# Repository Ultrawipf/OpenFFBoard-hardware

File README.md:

# OpenFFBoard-hardware
This contains the hardware designs of the OpenFFBoard

These are work in progress.
No guarantee for functionality or safety! The designs are experimental and may change at any time.
The firmware is available in the main [OpenFFBoard](https://github.com/Ultrawipf/OpenFFBoard) git.

This project requires soldering of many fine pitched parts including QFN. Availability of components may change over time so check for alternatives if something is not available.
The motor driver should be made with 2oz copper layers for best thermal performance!

The firmware may run on some third party development kits but as they have different pinouts and missing peripherals this is not recommended.

## Buy official kits
* [Elecrow](https://www.elecrow.com/open-ffboard-stm32f407-usb-interface-only.html)
* [Lectronz](https://www.lectronz.com/stores/gigawipf)
* [Tindie](https://www.tindie.com/stores/gigawipf/) or Discord.

Check the [Discord](https://discord.com/invite/gHtnEcP) and [project page](https://hackaday.io/project/163904-open-ffboard) for updates.

---

### LICENSE NOTE: The root license applies to all subfolders NOT containing their own LICENSE file. If a subfolder contains a different LICENSE file this different license applies to all subfolders below this LICENSE file.

**If you want to sell any hardware of this project yourself i would kindly ask you to get in contact with me ([mail](mailto:ffboard@y-richter.de) or Discord)**

## Changelog
### TMC Driver:

#### 1.1: (Prerelease prototype)
- Added filtering for Hall and Encoder inputs.
- Separated TMC and STM VM sense dividers

#### 1.2: (Major redesign)
- Using TMC4671-LA production version
- Added 5V buck converter
- Added emergency shutdown method by pulling enable low
- Rotated power stage. Moved all motor connectors to one side
- Moved analog encoder pins and routed differential inputs out
- Improved vcore impedance
- Increased encoder filter frequencies
- Reduced resistance of sense dividers
- Switched LM5050 to LM74700
- Space for 2 VM capacitors
- Improved mosfet protection
- Added temperature sensor pads on AGPI-B
- 50x50+100mm screw holes

#### 1.2 fix:
- Fixed silkscreen (R18 and R19 swapped)
- Modified some labels
- Added 33k gate pulldown for brake resistor
- Moved and resized vias in motor driver part (Manufacturing reliability)
- Tented vias

#### 1.2.2 (HALL):
- Redesigned power stage to use hall sensors (LEM GO SME and TMCS1100)
- Changed buffers to 74LV17APWJ
- Added opamp for TMC inputs (temperature and voltage sensing)
- Used opamp as comparator for hardware brake resistor activation point (~65V)
  
### 1.3.3:
- Analog section with separate LDO
- Support for more current sensors (ACS724)
- Optimized gate driver circuit w. resistors and diodes
- More separation between analog and power sections

### STM USB Interface:
#### 1.1:
- Initial prototype
- STM32F411RE based
- Only supports TMC4671 driver
- Only one SPI2 CS

#### 1.2:
- STM32F407VG
- Reserved PWM pins
- 3 CS pins per SPI
- CAN bus
- Reserved E-Stop
- USB Vbus sense
- separated ADCs for vsense and analog in
- LEDs moved
- Added FFBoard logo
- Changed USB diode to SMC
- Added zener pad on 5V
- Removed encoder buffer
- Higher value pwr led resistor

#### 1.2.1:
- Fixed some labels
- Moved USB socket and terminals slightly to the corners (Big usb plugs might interfere with the pins)
- Changed crystal load capacitors to lower values. (F407 DFU is very sensitive and does not work reliably with too high value caps)
- Added E-Stop capacitor against noise triggering it
- Tented vias

#### 1.2.2
- Swapped (Previously unused) Encoder Z pin from pin 65 to pin 62 because of interrupt conflicts with the DRV flag pin

#### 1.2.3
- USB-C instead of micro USB
- SPI1 uses a 2 row header
- Additional USB protections

#### 1.2.4
- Moved EXT header slightly
- Used 2 extra jumper pins for CAN termination instead of solderjumper

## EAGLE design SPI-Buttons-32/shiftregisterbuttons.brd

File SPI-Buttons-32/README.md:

# Shift register button module

This module allows the connection of up to 32 (or more if chained) buttons to any spi capable microcontroller or as a button source in the OpenFFBoard firmware.

### Connections
* V+ - 3,3V (or 5V)
* OUT - MISO of controller
* CS (Latch) - CS pin of controller
* CLK - SCK
* GND - GND

* IN - OUT of previous module
* Buttons between GND and any input pin

### Configuration in OpenFFBoard

Select SPI button source, select 74HC165 mode and invert buttons and the amount of used buttons (up to 32 for 1, up to 64 for 2 modules)

### CS options

In the default configuration MISO is active with CS HIGH (Bare 74HC165 compatible mode).
Connecting R34 instead of R33 changes this to CS LOW active (SPI compatible mode).
The tristate output mode can be disabled by removing R35.

Mode | R33 | R34 | R35
-|-|-|-
CS HIGH w. tristate | ✅ | ❌ | ✅
CS LOW w. tristate | ❌ | ✅ | ✅
CS HIGH wo. tristate | ✅ | ❌ | ❌
CS HIGH wo. tristate | ❌ | ✅ | ❌

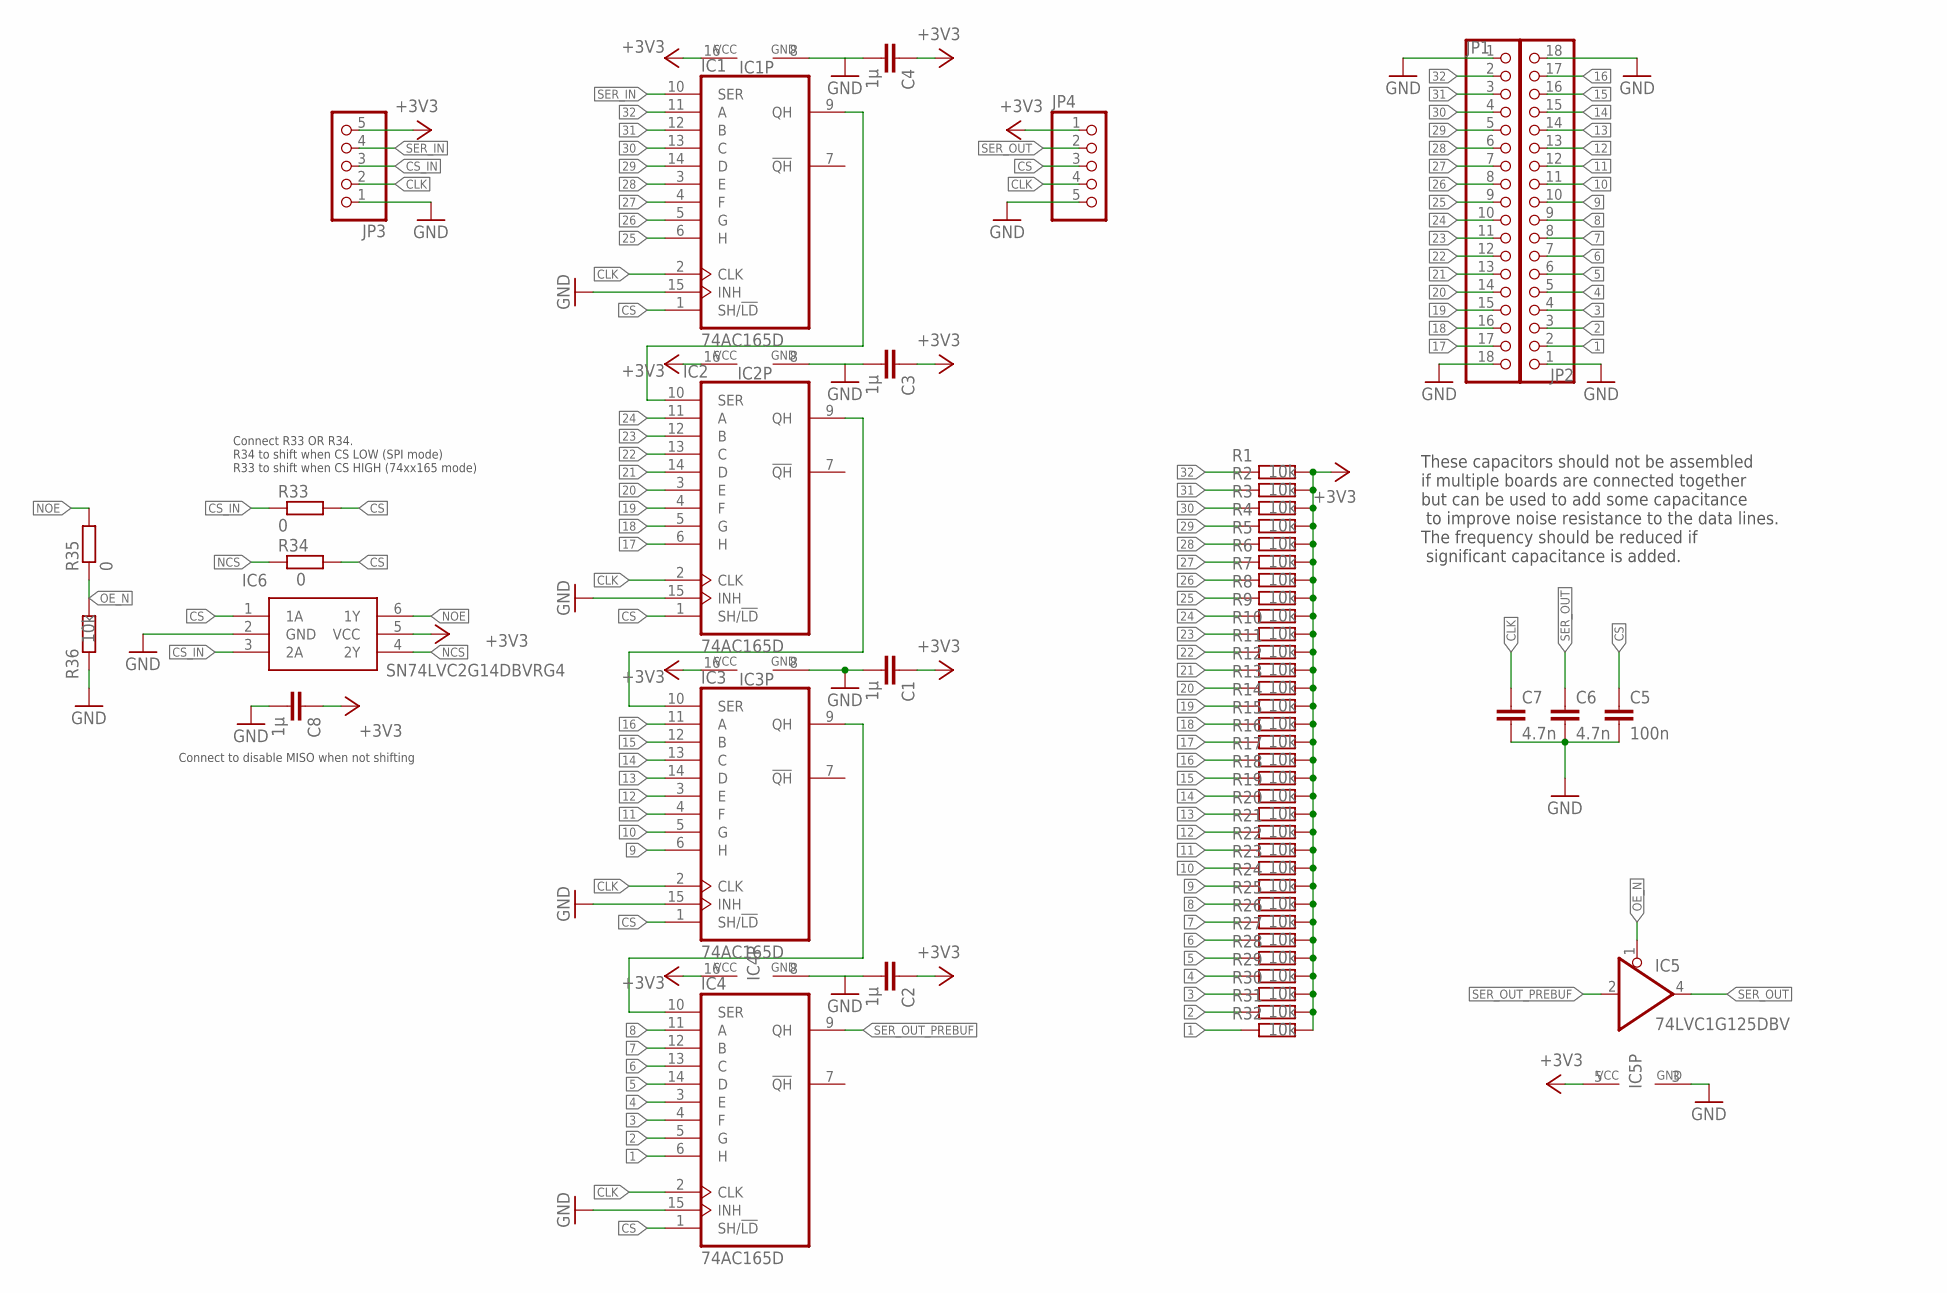
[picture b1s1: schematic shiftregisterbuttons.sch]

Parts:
C1, C2, C3, C4, C8: 1µ; C0603
C5: 100n; C0603
C6, C7: 4.7n; C0603
IC1, IC2, IC3, IC4: 74AC165D; SO16
IC5: 74LVC1G125DBV; SOT23-5
IC6: SN74LVC2G14DBVRG4; SOT95P280X145-6N
JP1, JP2: PINHD-1X18; 1X18
JP3, JP4: PINHD-1X5; 1X05
R1, R2, R3, R4, R5, R6, R7, R8, R9, R10, R11, R12, R13, R14, R15, R16, R17, R18, R19, R20, R21, R22, R23, R24, R25, R26, R27, R28, R29, R30, R31, R32, R36: 10k; R0603
R33, R34, R35: 0; R0603

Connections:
1: IC4.6 (H), JP2.2, R32.1
2: IC4.5 (G), JP2.3, R31.1
3: IC4.4 (F), JP2.4, R30.1
4: IC4.3 (E), JP2.5, R29.1
5: IC4.14 (D), JP2.6, R28.1
6: IC4.13 (C), JP2.7, R27.1
7: IC4.12 (B), JP2.8, R26.1
8: IC4.11 (A), JP2.9, R25.1
9: IC3.6 (H), JP2.10, R24.1
10: IC3.5 (G), JP2.11, R23.1
11: IC3.4 (F), JP2.12, R22.1
12: IC3.3 (E), JP2.13, R21.1
13: IC3.14 (D), JP2.14, R20.1
14: IC3.13 (C), JP2.15, R19.1
15: IC3.12 (B), JP2.16, R18.1
16: IC3.11 (A), JP2.17, R17.1
17: IC2.6 (H), JP1.17, R16.1
18: IC2.5 (G), JP1.16, R15.1
19: IC2.4 (F), JP1.15, R14.1
20: IC2.3 (E), JP1.14, R13.1
21: IC2.14 (D), JP1.13, R12.1
22: IC2.13 (C), JP1.12, R11.1
23: IC2.12 (B), JP1.11, R10.1
24: IC2.11 (A), JP1.10, R9.1
25: IC1.6 (H), JP1.9, R8.1
26: IC1.5 (G), JP1.8, R7.1
27: IC1.4 (F), JP1.7, R6.1
28: IC1.3 (E), JP1.6, R5.1
29: IC1.14 (D), JP1.5, R4.1
30: IC1.13 (C), JP1.4, R3.1
31: IC1.12 (B), JP1.3, R2.1
32: IC1.11 (A), JP1.2, R1.1
+3V3: C1.1, C2.1, C3.1, C4.1, C8.1, IC1.16 (VCC), IC2.16 (VCC), IC3.16 (VCC), IC4.16 (VCC), IC5.5 (VCC), IC6.5 (VCC), JP3.5, JP4.1, R1.2, R2.2, R3.2, R4.2, R5.2, R6.2, R7.2, R8.2, R9.2, R10.2, R11.2, R12.2, R13.2, R14.2, R15.2, R16.2, R17.2, R18.2, R19.2, R20.2, R21.2, R22.2, R23.2, R24.2, R25.2, R26.2, R27.2, R28.2, R29.2, R30.2, R31.2, R32.2
CLK: C7.1, IC1.2 (CLK), IC2.2 (CLK), IC3.2 (CLK), IC4.2 (CLK), JP3.2, JP4.4
CS: C5.1, IC1.1 (SH/!LD), IC2.1 (SH/!LD), IC3.1 (SH/!LD), IC4.1 (SH/!LD), IC6.1 (1A), JP4.3, R33.2, R34.2
CS_IN: IC6.3 (2A), JP3.3, R33.1
GND: C1.2, C2.2, C3.2, C4.2, C5.2, C6.2, C7.2, C8.2, IC1.8 (GND), IC1.15 (INH), IC2.8 (GND), IC2.15 (INH), IC3.8 (GND), IC3.15 (INH), IC4.8 (GND), IC4.15 (INH), IC5.3 (GND), IC6.2 (GND), JP1.1, JP1.18, JP2.1, JP2.18, JP3.1, JP4.5, R36.1
unnamed: IC2.9 (QH), IC3.10 (SER)
unnamed: IC3.9 (QH), IC4.10 (SER)
NCS: IC6.4 (2Y), R34.1
NOE: IC6.6 (1Y), R35.2
OE_N: IC5.1 (OE), R35.1, R36.2
SER1: IC1.9 (QH), IC2.10 (SER)
SER_IN: IC1.10 (SER), JP3.4
SER_OUT: C6.1, IC5.4 (O), JP4.2
SER_OUT_PREBUF: IC4.9 (QH), IC5.2 (I)

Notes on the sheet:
These capacitors should not be assembled if multiple boards are connected together but can be used to add some capacitance to improve noise resistance to the data lines. The frequency should be reduced if significant capacitance is added.
Connect to disable MISO when not shifting
Connect R33 OR R34. R34 to shift when CS LOW (SPI mode) R33 to shift when CS HIGH (74xx165 mode)

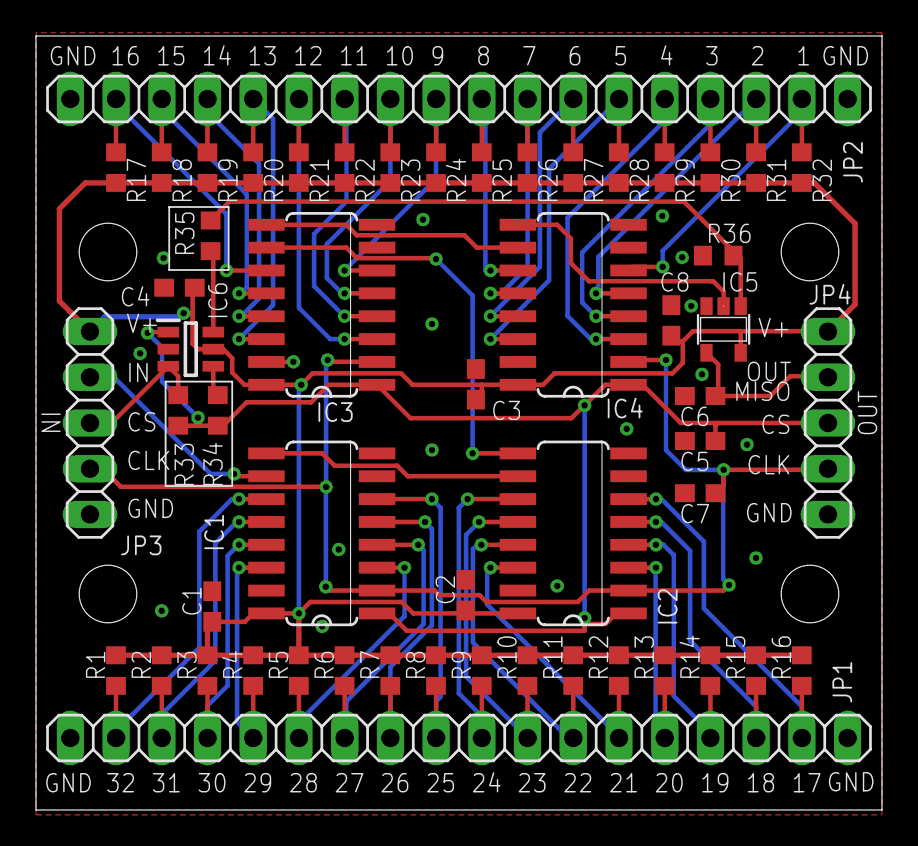
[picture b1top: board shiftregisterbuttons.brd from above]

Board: 2 copper layers, 47.0 x 43.0 mm, 54 parts (0 on the bottom side), 46 nets.

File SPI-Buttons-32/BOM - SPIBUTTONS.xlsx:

Comment | Designator | Footprint | LCSC Part #
1x18 pinheader | JP1, JP2 | 1X18
1x5 pinheader | JP3, JP4 | 1X05
10k resistor | R1, R2, R3, R4, R5, R6, R7, R8, R9, R10, R11, R12, R13, R14, R15, R16, R17, R18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 | R0603 | C25804
1µF capacitor | C1, C2, C3, C4,C8 | C0603 | C15849
74HC165D | IC1, IC2, IC3, IC4 | SO16 | C5613
0R | R35,R33 | R0603 | C21189
SN74LVC2G14DBV | IC6 | SOT23-6 | C12401
74LVC1G125DBV | IC5 | SOT23-5 | C23654

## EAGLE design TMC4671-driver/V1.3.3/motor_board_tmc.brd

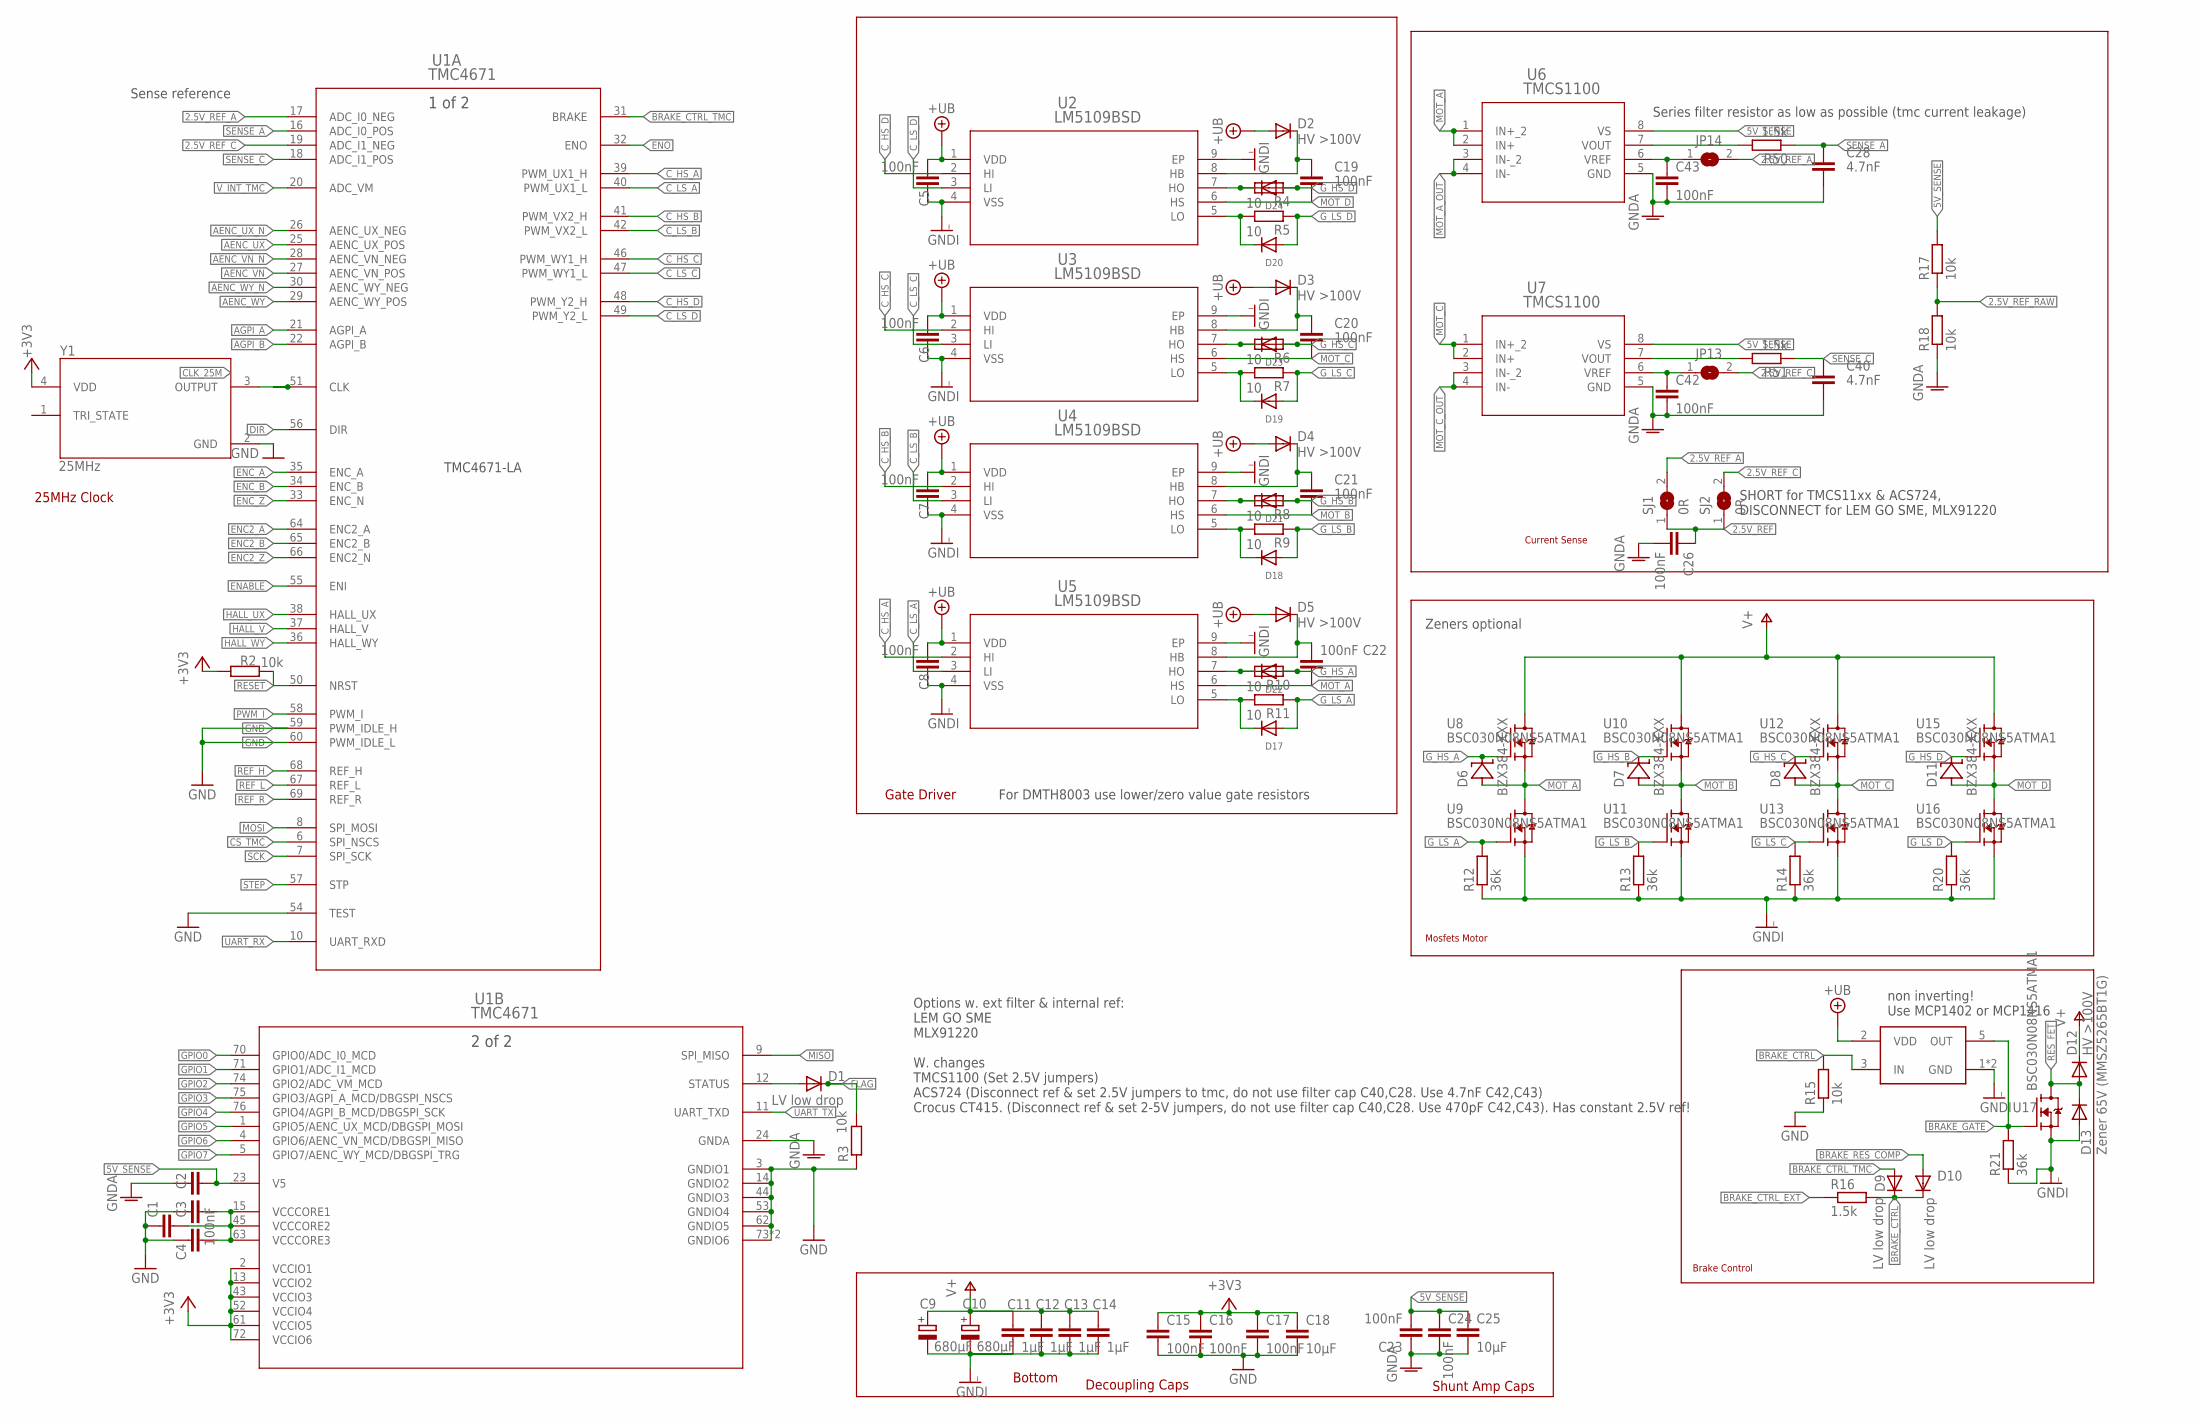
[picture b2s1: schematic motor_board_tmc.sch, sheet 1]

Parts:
C1, C3, C4, C5, C6, C7, C8, C15, C16, C17, C19, C20, C21, C22, C23, C24, C26, C42, C43: 100nF; C0603
C2, C18, C25: 10µF; C0805
C9, C10: 680µF; E7,5-16
C11, C12, C13, C14: 1µF; C1206
C28, C40: 4.7nF; C0603
D1, D9, D10: LV low drop; SOD-123FL
D2, D3, D4, D5, D12: HV >100V; SOD-123FL
D6, D7, D8, D11: BZX384-XXX; SOD323-R
D13: Zener 65V (MMSZ5265BT1G); SOD-123FL
D17, D18, D19, D20, D21, D22, D23, D24: DIODESOD-323F; SOD-323F
JP13, JP14: JUMPER-SMT_2_NO_SILK; RESISTOR_R0603
R2, R3, R15, R17, R18: 10k; R0603
R4, R5, R6, R7, R8, R9, R10, R11: 10; R0603
R12, R13, R14, R20, R21: 36k; R0603
R16, R50, R51: 1.5k; R0603
SJ1, SJ2: 0R; RESISTOR_R0603
U1: TMC4671; QFN76_10P5X6P5
U2, U3, U4, U5: LM5109BSD; SDC08A
U6, U7: TMCS1100; SOIC8_D_TEX
U8, U9, U10, U11, U12, U13, U15, U16, U17: BSC030N08NS5ATMA1; MOSFET_BSC093N04LSGATMA1
U14: MCP14XX; SOT23-5L
Y1: 25MHz; ECS-327KE-TR

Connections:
2.5V_REF: C26.1, SJ1.1, SJ2.1; also elsewhere on the board
2.5V_REF_A: JP14.2, SJ1.2, U1.17 (ADC_I0_NEG)
2.5V_REF_C: JP13.2, SJ2.2, U1.19 (ADC_I1_NEG)
2.5V_REF_RAW: R17.1, R18.2; also elsewhere on the board
5V_SENSE: C2.2, C23.2, C24.1, C25.1, R17.2, U1.23 (V5), U6.8 (VS), U7.8 (VS); also elsewhere on the board
+3V3: C15.1, C16.1, C17.1, C18.1, R2.2, U1.2 (VCCIO1), U1.13 (VCCIO2), U1.43 (VCCIO3), U1.52 (VCCIO4), U1.61 (VCCIO5), U1.72 (VCCIO6), Y1.4 (VDD); also elsewhere on the board
AENC_UX: U1.25 (AENC_UX_POS); also elsewhere on the board
AENC_UX_N: U1.26 (AENC_UX_NEG); also elsewhere on the board
AENC_VN: U1.27 (AENC_VN_POS); also elsewhere on the board
AENC_VN_N: U1.28 (AENC_VN_NEG); also elsewhere on the board
AENC_WY: U1.29 (AENC_WY_POS); also elsewhere on the board
AENC_WY_N: U1.30 (AENC_WY_NEG); also elsewhere on the board
AGPI_A: U1.21 (AGPI_A); also elsewhere on the board
AGPI_B: U1.22 (AGPI_B); also elsewhere on the board
BRAKE_CTRL: D9.C, D10.C, R15.2, R16.2, U14.3 (IN)
BRAKE_CTRL_EXT: R16.1; also elsewhere on the board
BRAKE_CTRL_TMC: D9.A, U1.31 (BRAKE)
BRAKE_GATE: R21.2, U14.5 (OUT), U17.4 (G)
BRAKE_RES_COMP: D10.A; also elsewhere on the board
CLK_25M: U1.51 (CLK), Y1.3 (OUTPUT)
CS_TMC: U1.6 (SPI_NSCS); also elsewhere on the board
C_HS_A: U1.39 (PWM_UX1_H), U5.2 (HI)
C_HS_B: U1.41 (PWM_VX2_H), U4.2 (HI)
C_HS_C: U1.46 (PWM_WY1_H), U3.2 (HI)
C_HS_D: U1.48 (PWM_Y2_H), U2.2 (HI)
C_LS_A: U1.40 (PWM_UX1_L), U5.3 (LI)
C_LS_B: U1.42 (PWM_VX2_L), U4.3 (LI)
C_LS_C: U1.47 (PWM_WY1_L), U3.3 (LI)
C_LS_D: U1.49 (PWM_Y2_L), U2.3 (LI)
DIR: U1.56 (DIR); also elsewhere on the board
ENABLE: U1.55 (ENI); also elsewhere on the board
ENC2_A: U1.64 (ENC2_A); also elsewhere on the board
ENC2_B: U1.65 (ENC2_B); also elsewhere on the board
ENC2_Z: U1.66 (ENC2_N); also elsewhere on the board
ENC_A: U1.35 (ENC_A); also elsewhere on the board
ENC_B: U1.34 (ENC_B); also elsewhere on the board
ENC_Z: U1.33 (ENC_N); also elsewhere on the board
ENO: U1.32 (ENO); also elsewhere on the board
FLAG: D1.C, R3.2; also elsewhere on the board
GND: C1.1, C3.1, C4.1, C15.2, C16.2, C17.2, C18.2, R3.1, R15.1, U1.3 (GNDIO1), U1.14 (GNDIO2), U1.44 (GNDIO3), U1.53 (GNDIO4), U1.54 (TEST), U1.59 (PWM_IDLE_H), U1.60 (PWM_IDLE_L), U1.62 (GNDIO5), U1.73 (GNDIO6), U1.77 (GNDIO6), Y1.2 (GND); also elsewhere on the board
GNDA: C2.1, C23.1, C24.2, C25.2, C26.2, C28.2, C40.2, C42.2, C43.2, R18.1, U1.24 (GNDA), U6.5 (GND), U7.5 (GND); also elsewhere on the board
GNDI: C5.1, C6.1, C7.1, C8.1, C9.-, C10.-, C11.2, C12.2, C13.2, C14.2, D13.A, R12.1, R13.1, R14.1, R20.1, R21.1, U2.4 (VSS), U2.9 (EP), U3.4 (VSS), U3.9 (EP), U4.4 (VSS), U4.9 (EP), U5.4 (VSS), U5.9 (EP), U9.1 (S), U9.2 (S), U9.3 (S), U11.1 (S), U11.2 (S), U11.3 (S), U13.1 (S), U13.2 (S), U13.3 (S), U14.1 (GND), U14.4 (GND), U16.1 (S), U16.2 (S), U16.3 (S), U17.1 (S), U17.2 (S), U17.3 (S); also elsewhere on the board
GPIO0: U1.70 (GPIO0/ADC_I0_MCD); also elsewhere on the board
GPIO1: U1.71 (GPIO1/ADC_I1_MCD); also elsewhere on the board
GPIO2: U1.74 (GPIO2/ADC_VM_MCD); also elsewhere on the board
GPIO3: U1.75 (GPIO3/AGPI_A_MCD/DBGSPI_NSCS); also elsewhere on the board
GPIO4: U1.76 (GPIO4/AGPI_B_MCD/DBGSPI_SCK); also elsewhere on the board
GPIO5: U1.1 (GPIO5/AENC_UX_MCD/DBGSPI_MOSI); also elsewhere on the board
GPIO6: U1.4 (GPIO6/AENC_VN_MCD/DBGSPI_MISO); also elsewhere on the board
GPIO7: U1.5 (GPIO7/AENC_WY_MCD/DBGSPI_TRG); also elsewhere on the board
G_HS_A: D6.C, D22.A, R10.1, U8.4 (G)
G_HS_B: D7.C, D21.A, R8.1, U10.4 (G)
G_HS_C: D8.C, D23.A, R6.1, U12.4 (G)
G_HS_D: D11.C, D24.A, R4.1, U15.4 (G)
G_LS_A: D17.A, R11.1, R12.2, U9.4 (G)
G_LS_B: D18.A, R9.1, R13.2, U11.4 (G)
G_LS_C: D19.A, R7.1, R14.2, U13.4 (G)
G_LS_D: D20.A, R5.1, R20.2, U16.4 (G)
HALL_UX: U1.38 (HALL_UX); also elsewhere on the board
HALL_V: U1.37 (HALL_V); also elsewhere on the board
HALL_WY: U1.36 (HALL_WY); also elsewhere on the board
MISO: U1.9 (SPI_MISO); also elsewhere on the board
MOSI: U1.8 (SPI_MOSI); also elsewhere on the board
MOT_A: C22.2, D6.A, U5.6 (HS), U6.1 (IN+_2), U6.2 (IN+), U8.1 (S), U8.2 (S), U8.3 (S), U9.5 (D)
MOT_A_OUT: U6.3 (IN-_2), U6.4 (IN-); also elsewhere on the board
MOT_B: C21.2, D7.A, U4.6 (HS), U10.1 (S), U10.2 (S), U10.3 (S), U11.5 (D); also elsewhere on the board
MOT_C: C20.2, D8.A, U3.6 (HS), U7.1 (IN+_2), U7.2 (IN+), U12.1 (S), U12.2 (S), U12.3 (S), U13.5 (D)
MOT_C_OUT: U7.3 (IN-_2), U7.4 (IN-); also elsewhere on the board
MOT_D: C19.2, D11.A, U2.6 (HS), U15.1 (S), U15.2 (S), U15.3 (S), U16.5 (D); also elsewhere on the board
unnamed: D1.A, U1.12 (STATUS)
unnamed: D17.C, R11.2, U5.5 (LO)
unnamed: C22.1, D5.C, U5.8 (HB)
unnamed: D22.C, R10.2, U5.7 (HO)
unnamed: C21.1, D4.C, U4.8 (HB)
unnamed: D18.C, R9.2, U4.5 (LO)
unnamed: D21.C, R8.2, U4.7 (HO)
unnamed: C19.1, D2.C, U2.8 (HB)
unnamed: D20.C, R5.2, U2.5 (LO)
unnamed: D24.C, R4.2, U2.7 (HO)
unnamed: C20.1, D3.C, U3.8 (HB)
unnamed: D19.C, R7.2, U3.5 (LO)
unnamed: D23.C, R6.2, U3.7 (HO)
PWM_I: U1.58 (PWM_I); also elsewhere on the board
REF_H: U1.68 (REF_H); also elsewhere on the board
REF_L: U1.67 (REF_L); also elsewhere on the board
REF_R: U1.69 (REF_R); also elsewhere on the board
RESET: R2.1, U1.50 (NRST); also elsewhere on the board
RES_FET: D12.A, D13.C, U17.5 (D); also elsewhere on the board
SCK: U1.7 (SPI_SCK); also elsewhere on the board
SENSE_A: C28.1, R50.1, U1.16 (ADC_I0_POS)
SENSE_A_RAW: R50.2, U6.7 (VOUT)
SENSE_C: C40.1, R51.1, U1.18 (ADC_I1_POS)
SENSE_C_RAW: R51.2, U7.7 (VOUT)
STEP: U1.57 (STP); also elsewhere on the board
UART_RX: U1.10 (UART_RXD); also elsewhere on the board
UART_TX: U1.11 (UART_TXD); also elsewhere on the board
V+: C9.+, C10.+, C11.1, C12.1, C13.1, C14.1, D12.C, U8.5 (D), U10.5 (D), U12.5 (D), U15.5 (D); also elsewhere on the board
VCORE: C1.2, C3.2, C4.2, U1.15 (VCCCORE1), U1.45 (VCCCORE2), U1.63 (VCCCORE3)
VREF_A_RAW: C43.1, JP14.1, U6.6 (VREF)
VREF_C_RAW: C42.1, JP13.1, U7.6 (VREF)
V_GD: C5.2, C6.2, C7.2, C8.2, D2.A, D3.A, D4.A, D5.A, U2.1 (VDD), U3.1 (VDD), U4.1 (VDD), U5.1 (VDD), U14.2 (VDD); also elsewhere on the board
V_INT_TMC: U1.20 (ADC_VM); also elsewhere on the board

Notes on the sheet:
Mosfets Motor
Gate Driver
Current Sense
Brake Control
Shunt Amp Caps
Decoupling Caps
25MHz Clock
Bottom
Sense reference
Zeners optional
TMC4671-LA
non inverting! Use MCP1402 or MCP1416
SHORT for TMCS11xx & ACS724, DISCONNECT for LEM GO SME, MLX91220
Options w. ext filter & internal ref: LEM GO SME MLX91220 W. changes TMCS1100 (Set 2.5V jumpers) ACS724 (Disconnect ref & set 2.5V jumpers to tmc, do not use filter cap C40,C28. Use 4.7nF C42,C43) Crocus CT415. (Disconnect ref & set 2-5V jumpers, do not use filter cap C40,C28. Use 470pF C42,C43). H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
Series filter resistor as low as possible (tmc current leakage)
For DMTH8003 use lower/zero value gate resistors

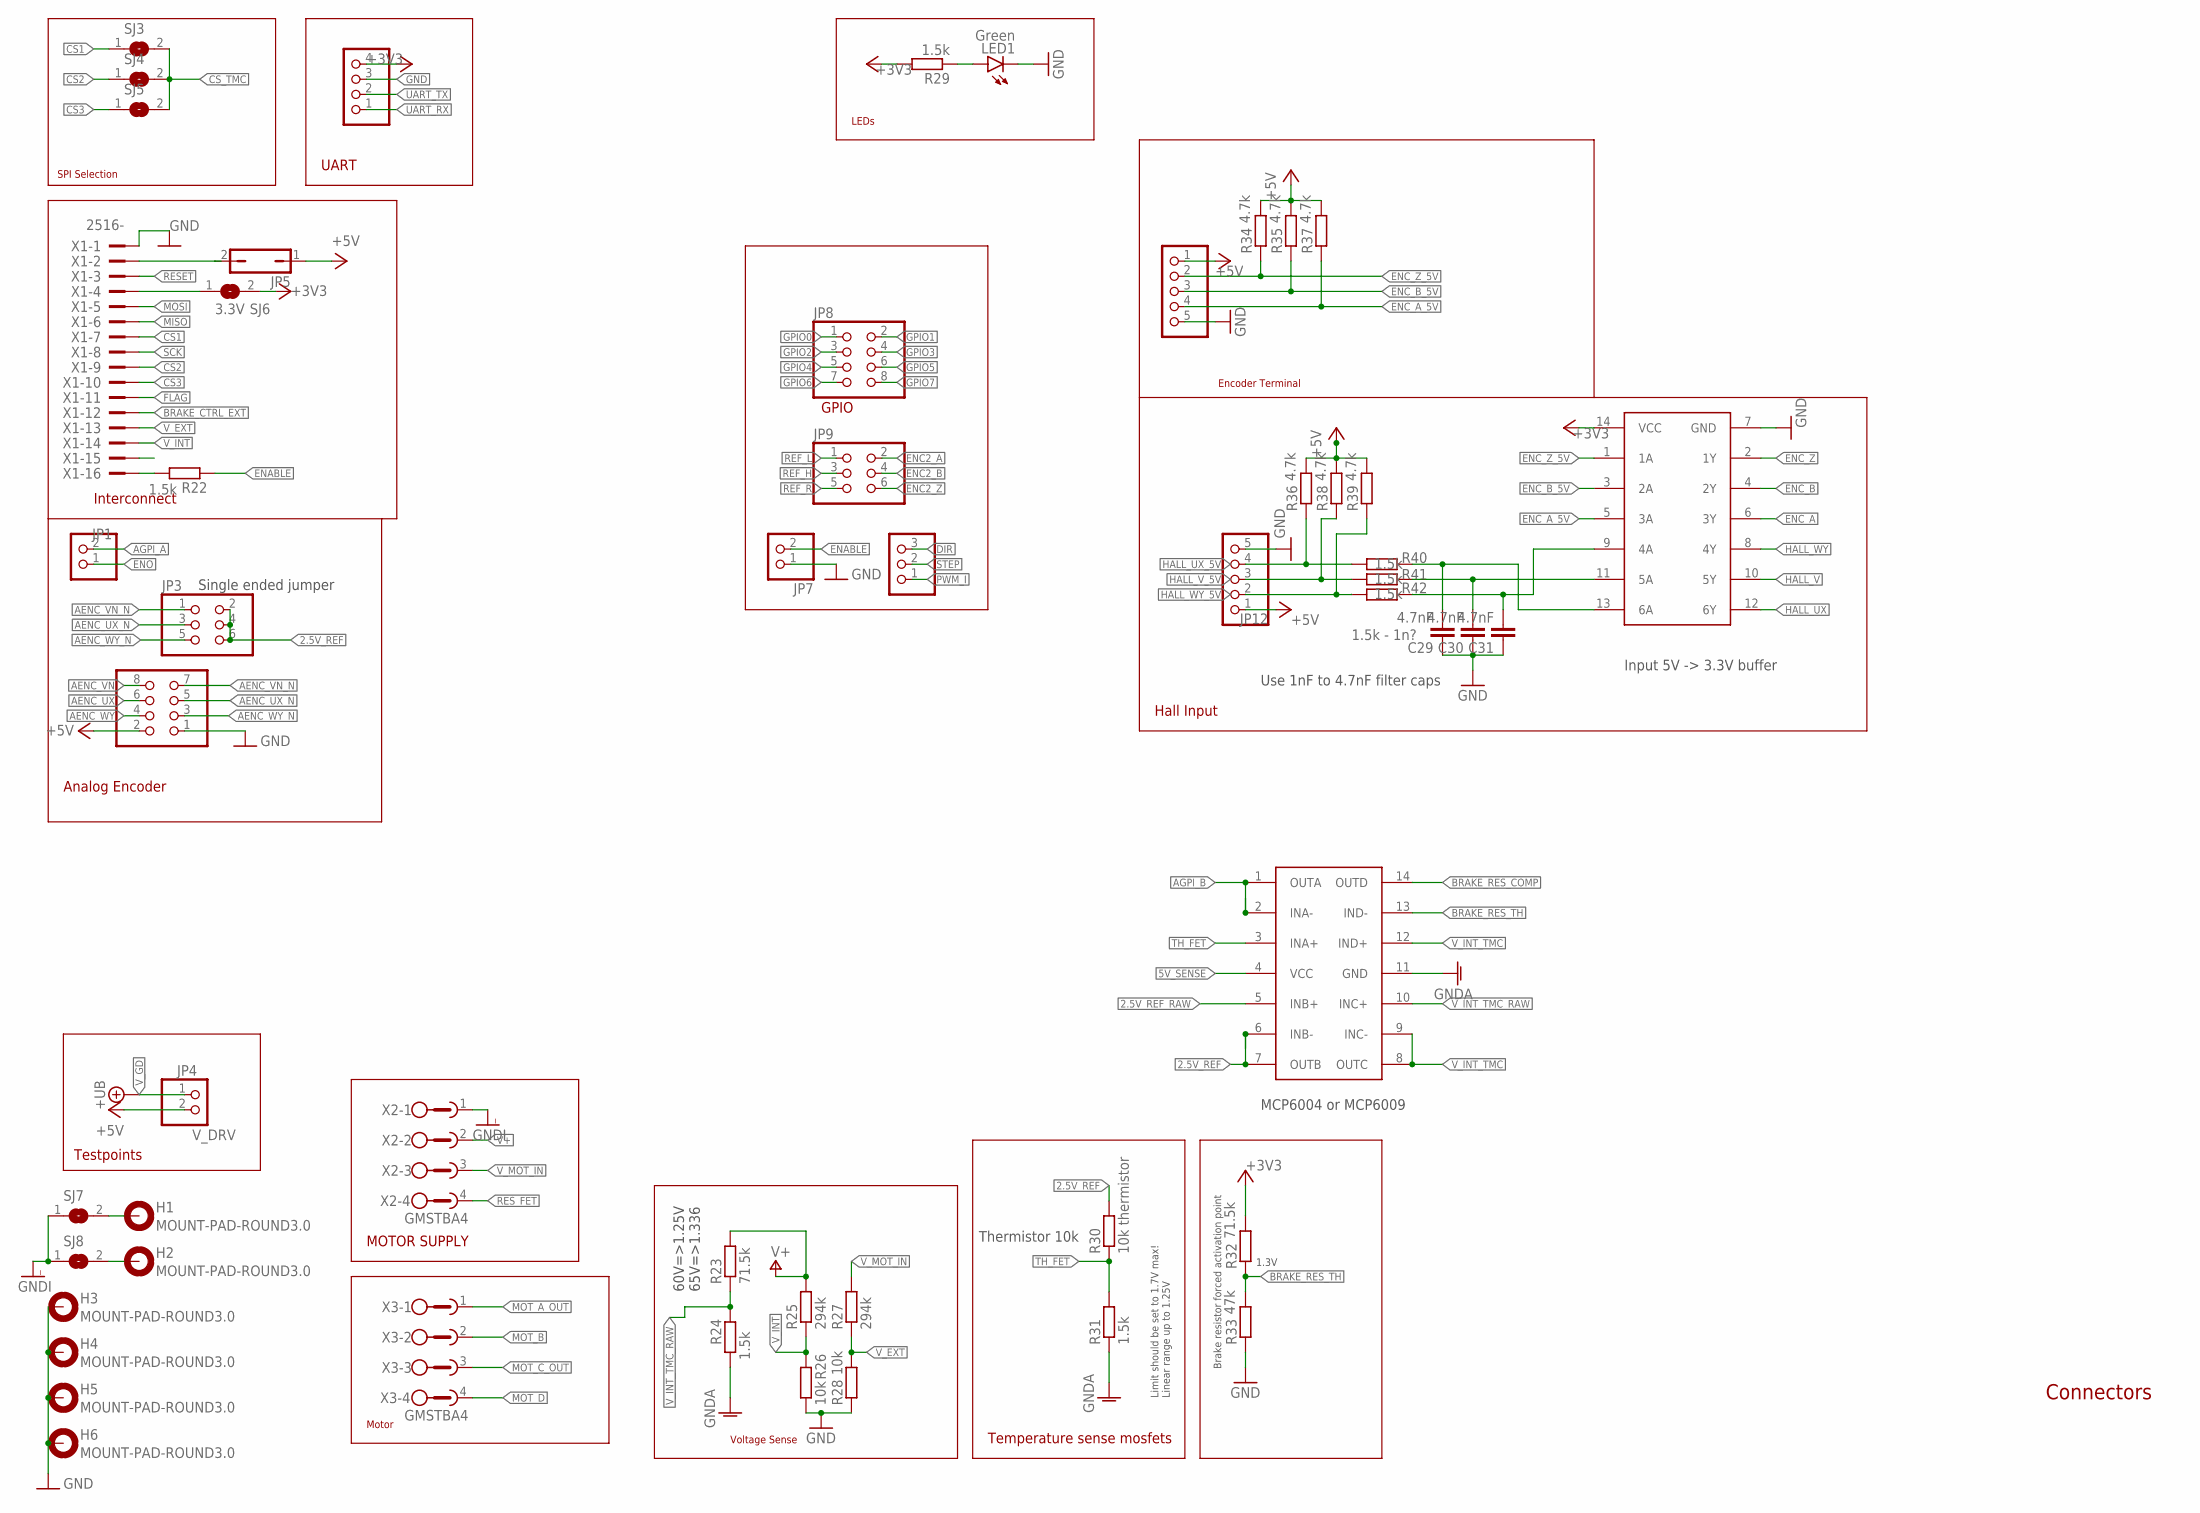
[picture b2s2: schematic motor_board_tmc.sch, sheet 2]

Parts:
C29, C30, C31: 4.7nF; C0603
H1, H2, H3, H4, H5, H6: MOUNT-PAD-ROUND3.0; 3,0-PAD
JP1, JP7: PINHD-1X2; 1X02
JP2, JP8: PINHD-2X4; 2X04
JP3, JP9: PINHD-2X3; 2X03
JP4: V_DRV; 1X02
JP5: JP1Q; JP1
JP6: PINHD-1X4; 1X04
JP10: PINHD-1X3; 1X03
JP11, JP12: PINHD-1X5; 1X05
LED1: Green; SML0805
R22, R24, R29, R31, R40, R41, R42: 1.5k; R0603
R23, R32: 71.5k; R0805
R25, R27: 294k; R0805
R26, R28: 10k; R0603
R30: 10k thermistor; R0603
R33: 47k; R0603
R34, R35, R36, R37, R38, R39: 4.7k; R0603
SJ3, SJ4, SJ5, SJ7, SJ8: SJ
SJ6: 3.3V; SJ
U18: MCP6004; TSSOP14
U19: 74LV17APWJ; TSSOP14
X1: 2516-; PAK100/2500-16
X2, X3: GMSTBA4

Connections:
2.5V_REF: JP3.2, JP3.4, JP3.6, R30.2, U18.6 (INB-), U18.7 (OUTB); also elsewhere on the board
2.5V_REF_RAW: U18.5 (INB+); also elsewhere on the board
5V_SENSE: U18.4 (VCC); also elsewhere on the board
+3V3: JP6.4, R29.2, R32.2, SJ6.2, U19.14 (VCC); also elsewhere on the board
+5V: JP2.2, JP4.2, JP5.1, JP11.1, JP12.1, R34.2, R35.2, R36.2, R37.2, R38.2, R39.2; also elsewhere on the board
AENC_UX: JP2.6; also elsewhere on the board
AENC_UX_N: JP2.5, JP3.3; also elsewhere on the board
AENC_VN: JP2.8; also elsewhere on the board
AENC_VN_N: JP2.7, JP3.1; also elsewhere on the board
AENC_WY: JP2.4; also elsewhere on the board
AENC_WY_N: JP2.3, JP3.5; also elsewhere on the board
AGPI_A: JP1.2; also elsewhere on the board
AGPI_B: U18.1 (OUTA), U18.2 (INA-); also elsewhere on the board
BRAKE_CTRL_EXT: X1.12; also elsewhere on the board
BRAKE_RES_COMP: U18.14 (OUTD); also elsewhere on the board
BRAKE_RES_TH: R32.1, R33.2, U18.13 (IND-)
CS1: SJ3.1, X1.7
CS2: SJ4.1, X1.9
CS3: SJ5.1, X1.10
CS_TMC: SJ3.2, SJ4.2, SJ5.2; also elsewhere on the board
DIR: JP10.3; also elsewhere on the board
ENABLE: JP7.2, R22.1; also elsewhere on the board
ENC2_A: JP9.2; also elsewhere on the board
ENC2_B: JP9.4; also elsewhere on the board
ENC2_Z: JP9.6; also elsewhere on the board
ENC_A: U19.6 (3Y); also elsewhere on the board
ENC_A_5V: JP11.4, R37.1, U19.5 (3A)
ENC_B: U19.4 (2Y); also elsewhere on the board
ENC_B_5V: JP11.3, R35.1, U19.3 (2A)
ENC_Z: U19.2 (1Y); also elsewhere on the board
ENC_Z_5V: JP11.2, R34.1, U19.1 (1A)
ENO: JP1.1; also elsewhere on the board
FLAG: X1.11; also elsewhere on the board
GND: C29.1, C30.1, C31.1, H3.B3,0, H4.B3,0, H5.B3,0, H6.B3,0, JP2.1, JP6.3, JP7.1, JP11.5, JP12.5, LED1.C, R26.1, R28.1, R33.1, U19.7 (GND), X1.1; also elsewhere on the board
GNDA: R24.1, R31.1, U18.11 (GND); also elsewhere on the board
GNDI: SJ7.1, SJ8.1, X2.1; also elsewhere on the board
GPIO0: JP8.1; also elsewhere on the board
GPIO1: JP8.2; also elsewhere on the board
GPIO2: JP8.3; also elsewhere on the board
GPIO3: JP8.4; also elsewhere on the board
GPIO4: JP8.5; also elsewhere on the board
GPIO5: JP8.6; also elsewhere on the board
GPIO6: JP8.7; also elsewhere on the board
GPIO7: JP8.8; also elsewhere on the board
HALL_UX: U19.12 (6Y); also elsewhere on the board
HALL_UX_5V: C29.2, R40.1, U19.13 (6A)
HALL_V: U19.10 (5Y); also elsewhere on the board
HALL_V_5V: C30.2, R41.1, U19.11 (5A)
HALL_WY: U19.8 (4Y); also elsewhere on the board
HALL_WY_5V: C31.2, R42.1, U19.9 (4A)
MISO: X1.6; also elsewhere on the board
MOSI: X1.5; also elsewhere on the board
MOT_A_OUT: X3.1; also elsewhere on the board
MOT_B: X3.2; also elsewhere on the board
MOT_C_OUT: X3.3; also elsewhere on the board
MOT_D: X3.4; also elsewhere on the board
unnamed: JP12.4, R36.1, R40.2
unnamed: JP12.3, R38.1, R41.2
unnamed: H1.B3,0, SJ7.2
unnamed: LED1.A, R29.1
unnamed: JP5.2, X1.2
unnamed: H2.B3,0, SJ8.2
unnamed: JP12.2, R39.1, R42.2
unnamed: R22.2, X1.16
unnamed: SJ6.1, X1.4
PWM_I: JP10.1; also elsewhere on the board
REF_H: JP9.3; also elsewhere on the board
REF_L: JP9.1; also elsewhere on the board
REF_R: JP9.5; also elsewhere on the board
RESET: X1.3; also elsewhere on the board
RES_FET: X2.4; also elsewhere on the board
SCK: X1.8; also elsewhere on the board
STEP: JP10.2; also elsewhere on the board
TH_FET: R30.1, R31.2, U18.3 (INA+)
UART_RX: JP6.1; also elsewhere on the board
UART_TX: JP6.2; also elsewhere on the board
V+: R23.2, R25.2, X2.2; also elsewhere on the board
V_EXT: R27.1, R28.2, X1.13
V_GD: JP4.1; also elsewhere on the board
V_INT: R25.1, R26.2, X1.14
V_INT_TMC: U18.8 (OUTC), U18.9 (INC-), U18.12 (IND+); also elsewhere on the board
V_INT_TMC_RAW: R23.1, R24.2, U18.10 (INC+)
V_MOT_IN: R27.2, X2.3; also elsewhere on the board

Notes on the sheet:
Motor
Encoder Terminal
Hall Input
GPIO
MOTOR SUPPLY
Interconnect
UART
SPI Selection
LEDs
Connectors
Testpoints
Analog Encoder
Single ended jumper
1.5k - 1n?
Input 5V -> 3.3V buffer
MCP6004 or MCP6009
Voltage Sense
60V=>1.25V 65V=>1.336
Temperature sense mosfets
Thermistor 10k
Brake resistor forced activation point
Limit should be set to 1.7V max! Linear range up to 1.25V
1.3V
Use 1nF to 4.7nF filter caps

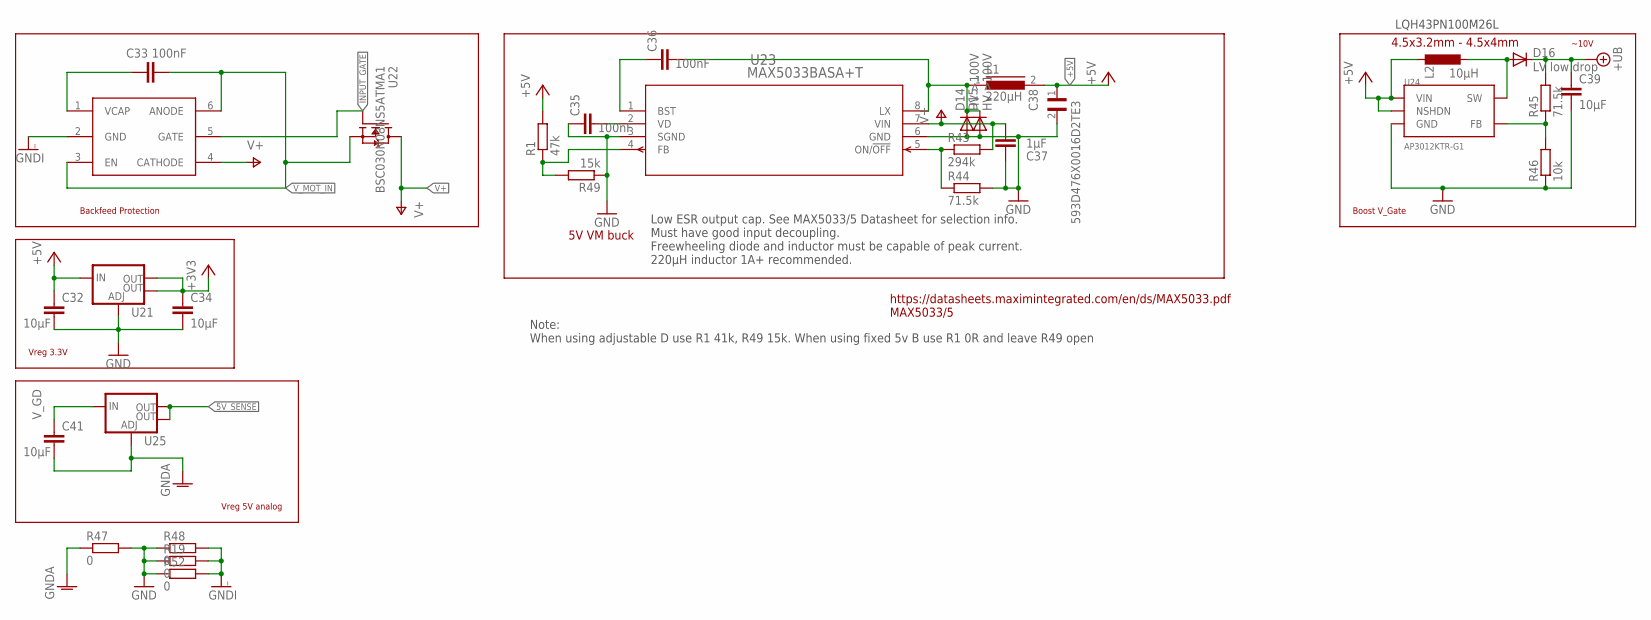
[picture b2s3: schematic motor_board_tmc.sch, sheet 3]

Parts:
C32, C34, C39, C41: 10µF; C0805
C33, C35, C36: 100nF; C0603
C37: 1µF; C1206
C38: 593D476X0016D2TE3; CAPPM7343X310N
D14: HV >100V; SOD-123FL
D15: HV >100V; SMADIODE
D16: LV low drop; SOD-123FL
L1: 220µH; 8MMINDUCTOR
L2: 10µH; L4532P
R1: 47k; R0603
R19, R47, R48, R52: 0; R0603
R43: 294k; R0805
R44, R45: 71.5k; R0805
R46: 10k; R0603
R49: 15k; R0603
U20: LM74700-Q1; SOT23-6
U21, U25: V_REG_LM1117SOT223; SOT223
U22: BSC030N08NS5ATMA1; MOSFET_BSC093N04LSGATMA1
U23: MAX5033BASA+T; 21-0041B_8_MXM
U24: AP3012KTR-G1; SOT23-5L

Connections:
5V_SENSE: U25.2 (OUT), U25.4 (OUT); also elsewhere on the board
+3V3: C34.1, U21.2 (OUT), U21.4 (OUT); also elsewhere on the board
+5V: C32.1, C38.1, L1.2, L2.1, R1.2, U21.3 (IN), U24.4 (NSHDN), U24.5 (VIN); also elsewhere on the board
GND: C32.2, C34.2, C35.1, C37.1, C38.2, C39.2, D14.A, D15.A, R19.1, R44.2, R46.1, R47.2, R48.1, R49.1, R52.1, U21.1 (ADJ), U23.3 (SGND), U23.6 (GND), U24.2 (GND); also elsewhere on the board
GNDA: C41.2, R47.1, U25.1 (ADJ); also elsewhere on the board
GNDI: R19.2, R48.2, R52.2, U20.2 (GND); also elsewhere on the board
INPUT_GATE: U20.5 (GATE), U22.4 (G)
unnamed: R45.1, R46.2, U24.3 (FB)
unnamed: R1.1, R49.2, U23.4 (FB)
unnamed: D16.A, L2.2, U24.1 (SW)
unnamed: C36.2, D14.C, D15.C, L1.1, U23.8 (LX)
unnamed: C36.1, U23.1 (BST)
unnamed: R43.1, R44.1, U23.5 (ON/!OFF)
unnamed: C33.1, U20.1 (VCAP)
unnamed: C35.2, U23.2 (VD)
V+: C37.2, R43.2, U20.4 (CATHODE), U22.5 (D), U23.7 (VIN); also elsewhere on the board
V_GD: C39.1, C41.1, D16.C, R45.2, U25.3 (IN); also elsewhere on the board
V_MOT_IN: C33.2, U20.3 (EN), U20.6 (ANODE), U22.1 (S), U22.2 (S), U22.3 (S); also elsewhere on the board

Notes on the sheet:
Vreg 3.3V
Backfeed Protection
Boost V_Gate
~10V
4.5x3.2mm - 4.5x4mm
5V VM buck
https://datasheets.maximintegrated.com/en/ds/MAX5033.pdf MAX5033/5
LQH43PN100M26L
Low ESR output cap. See MAX5033/5 Datasheet for selection info. Must have good input decoupling. Freewheeling diode and inductor must be capable of peak current. 220µH inductor 1A+ recommended.
Vreg 5V analog
Note: When using adjustable D use R1 41k, R49 15k. When using fixed 5v B use R1 0R and leave R49 open

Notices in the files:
parts and their libraries:
SparkFun-Jumpers: Licensing: Creative Commons ShareAlike 4.0 International - https://creativecommons.org/licenses/by-sa/4.0
COPYRIGHT: Copyright (C) 2018 Accelerated Designs. All rights reserved
